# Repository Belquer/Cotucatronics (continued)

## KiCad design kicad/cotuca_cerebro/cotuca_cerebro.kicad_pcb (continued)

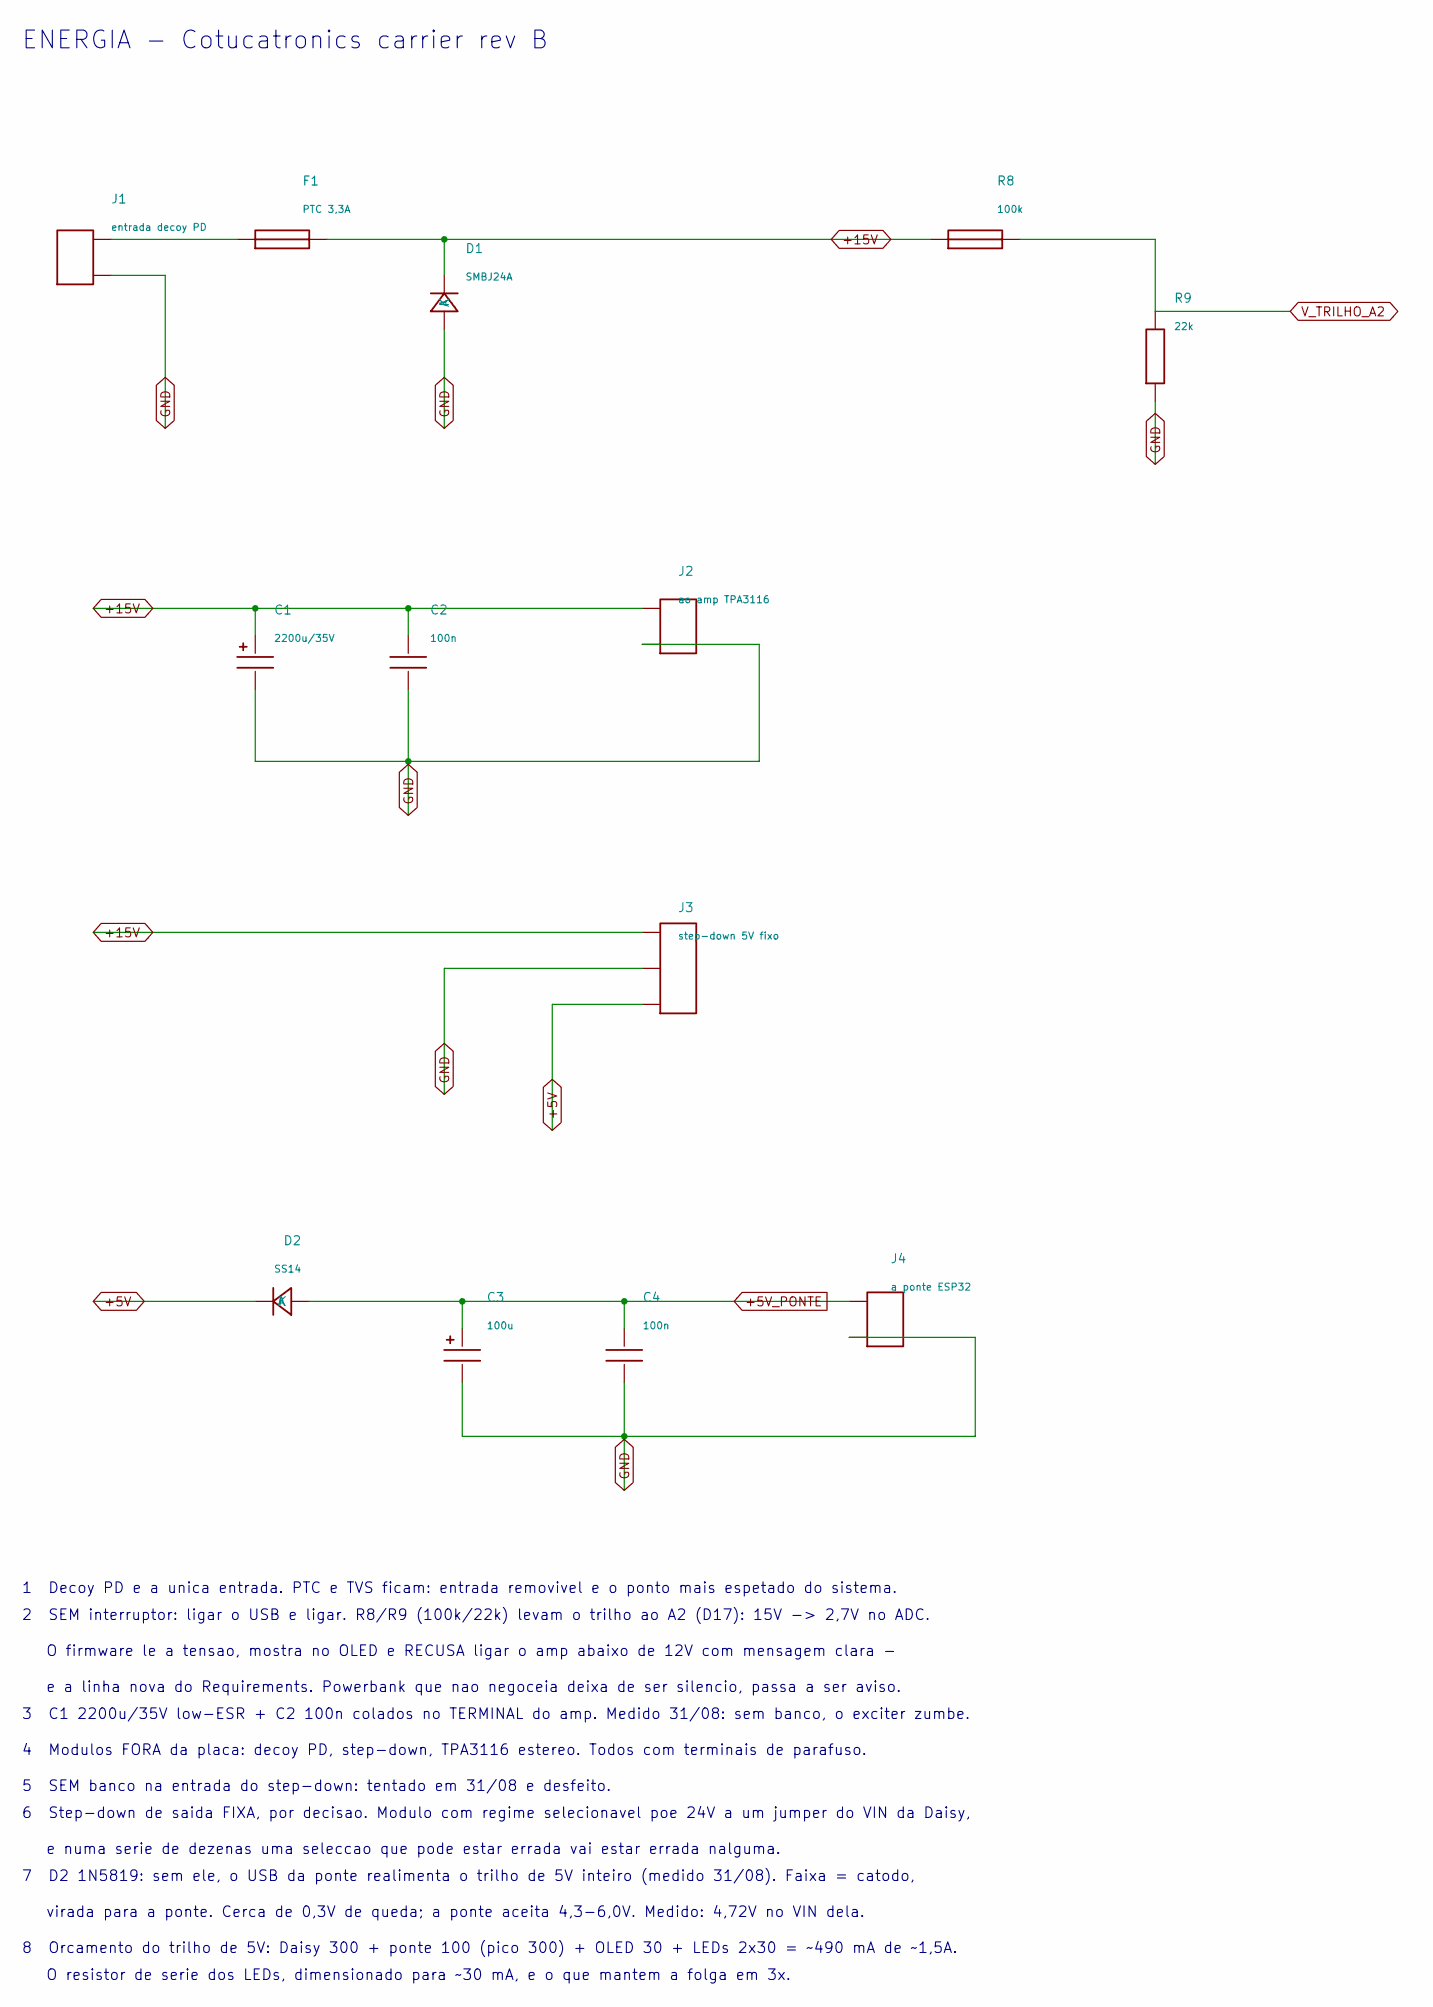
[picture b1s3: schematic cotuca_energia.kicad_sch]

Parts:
C1: 2200u/35V; CP_Radial_D16.0mm_P7.50mm; MPN EEU-FR1V222
C2, C4: 100n; C_0805_2012Metric
C3: 100u; CP_Radial_D6.3mm_P2.50mm; MPN EEU-FR1C101
D1: SMBJ24A; D_SMB; MPN SMBJ24A
D2: SS14; D_SMA; MPN SS14
F1: PTC 3,3A; Fuse_2920_7451Metric; MPN MF-LSMF300/24X-2
J1: entrada decoy PD; TerminalBlock_Phoenix_MKDS-1,5-2-5.08_1x02_P5.08mm_Horizont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; MPN 1715721
J2: ao amp TPA3116; TerminalBlock_Phoenix_MKDS-1,5-2-5.08_1x02_P5.08mm_Horizont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; MPN 1715721
J3: step-down 5V fixo; PinHeader_1x03_P2.54mm_Vertical; MPN 61304011121
J4: a ponte ESP32; PinHeader_1x02_P2.54mm_Vertical; MPN 61304011121
R8: 100k; R_0805_2012Metric
R9: 22k; R_0805_2012Metric

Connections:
+5V: D2.2 (A), J3.3; also elsewhere on the board
+5V_PONTE: C3.1, C4.1, D2.1 (K), J4.1; also elsewhere on the board
+15V: C1.1, C2.1, D1.1 (K), F1.2, J2.1, J3.1, R8.1; also elsewhere on the board
GND: C1.2, C2.2, C3.2, C4.2, D1.2 (A), J1.2, J2.2, J3.2, J4.2, R9.2; also elsewhere on the board
unnamed: F1.1, J1.1
V_TRILHO_A2: R8.2, R9.1; also elsewhere on the board

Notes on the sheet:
3 C1 2200u/35V low-ESR + C2 100n colados no TERMINAL do amp. Medido 31/08: sem banco, o exciter zumbe.
virada para a ponte. Cerca de 0,3V de queda; a ponte aceita 4,3-6,0V. Medido: 4,72V no VIN dela.
6 Step-down de saida FIXA, por decisao. Modulo com regime selecionavel poe 24V a um jumper do VIN da Daisy,
e numa serie de dezenas uma seleccao que pode estar errada vai estar errada nalguma.
O firmware le a tensao, mostra no OLED e RECUSA ligar o amp abaixo de 12V com mensagem clara -
5 SEM banco na entrada do step-down: tentado em 31/08 e desfeito.
8 Orcamento do trilho de 5V: Daisy 300 + ponte 100 (pico 300) + OLED 30 + LEDs 2x30 = ~490 mA de ~1,5A.
e a linha nova do Requirements. Powerbank que nao negoceia deixa de ser silencio, passa a ser aviso.
1 Decoy PD e a unica entrada. PTC e TVS ficam: entrada removivel e o ponto mais espetado do sistema.
2 SEM interruptor: ligar o USB e ligar. R8/R9 (100k/22k) levam o trilho ao A2 (D17): 15V -> 2,7V no ADC.
7 D2 1N5819: sem ele, o USB da ponte realimenta o trilho de 5V inteiro (medido 31/08). Faixa = catodo,
4 Modulos FORA da placa: decoy PD, step-down, TPA3116 estereo. Todos com terminais de parafuso.
ENERGIA - Cotucatronics carrier rev B
O resistor de serie dos LEDs, dimensionado para ~30 mA, e o que mantem a folga em 3x.

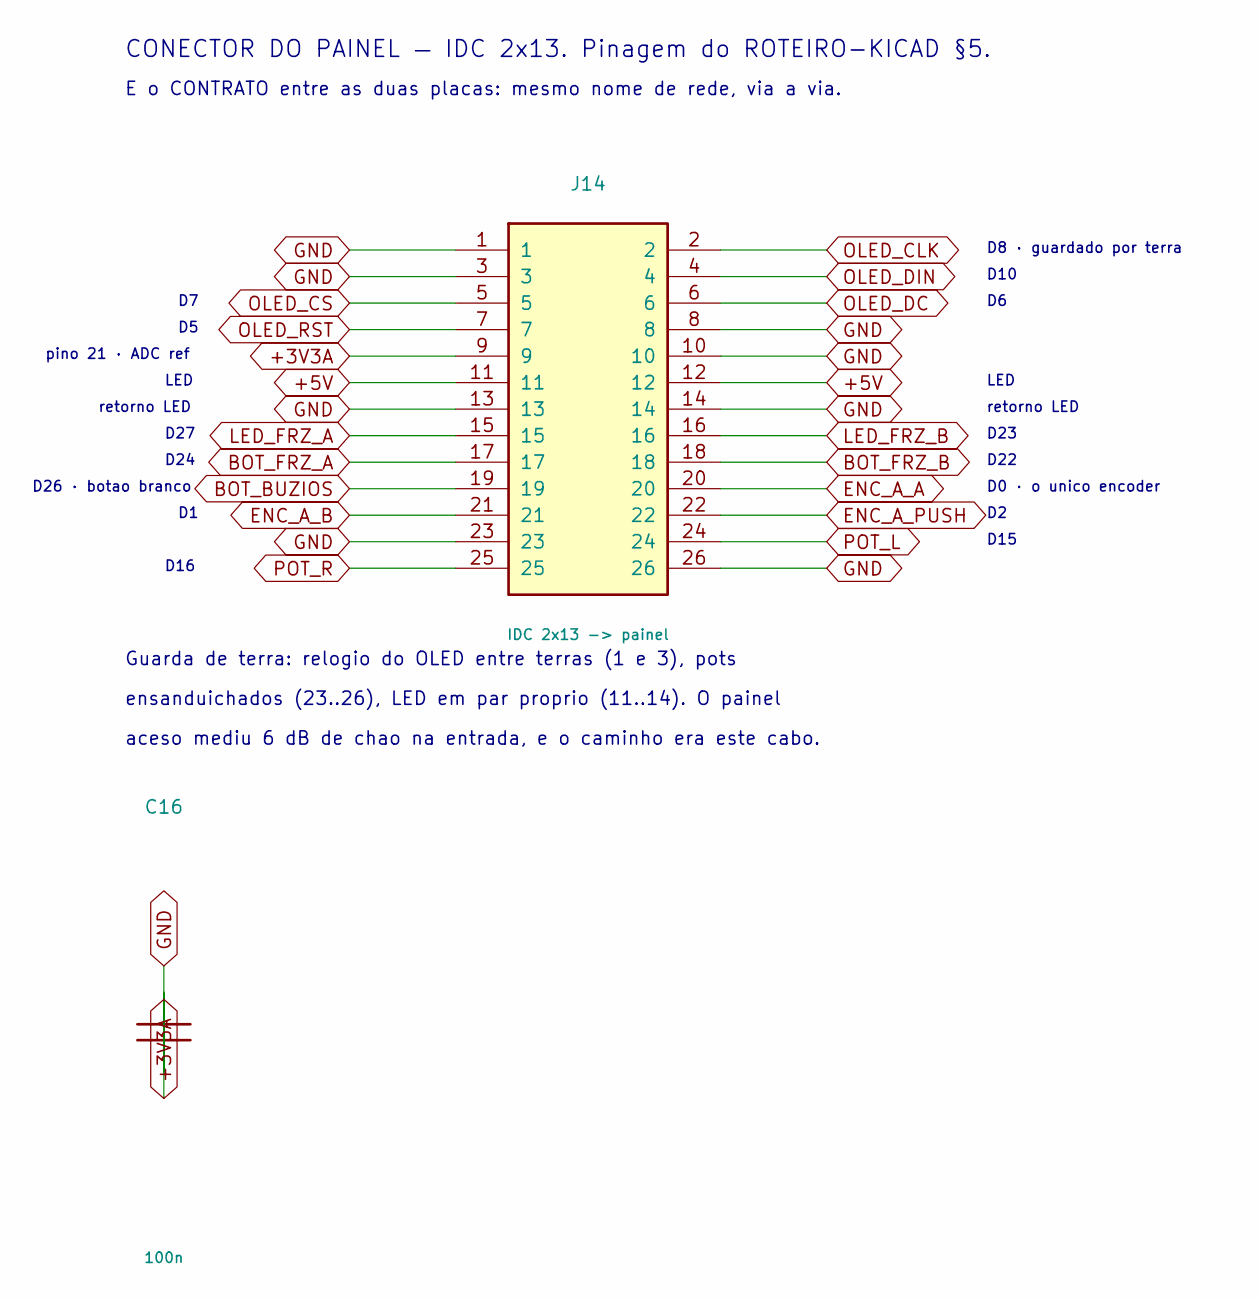
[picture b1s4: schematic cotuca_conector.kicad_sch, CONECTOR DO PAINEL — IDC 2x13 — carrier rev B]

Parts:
C16: 100n; C_0805_2012Metric
J14: IDC 2x13 -> painel; IDC-Header_2x13_P2.54mm_Vertical; MPN 61202621621

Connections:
+3V3A: C16.1, J14.9; also elsewhere on the board
+5V: J14.11, J14.12; also elsewhere on the board
BOT_BUZIOS: J14.19; also elsewhere on the board
BOT_FRZ_A: J14.17; also elsewhere on the board
BOT_FRZ_B: J14.18; also elsewhere on the board
ENC_A_A: J14.20; also elsewhere on the board
ENC_A_B: J14.21; also elsewhere on the board
ENC_A_PUSH: J14.22; also elsewhere on the board
GND: C16.2, J14.1, J14.3, J14.8, J14.10, J14.13, J14.14, J14.23, J14.26; also elsewhere on the board
LED_FRZ_A: J14.15; also elsewhere on the board
LED_FRZ_B: J14.16; also elsewhere on the board
OLED_CLK: J14.2; also elsewhere on the board
OLED_CS: J14.5; also elsewhere on the board
OLED_DC: J14.6; also elsewhere on the board
OLED_DIN: J14.4; also elsewhere on the board
OLED_RST: J14.7; also elsewhere on the board
POT_L: J14.24; also elsewhere on the board
POT_R: J14.25; also elsewhere on the board

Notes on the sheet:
D8 · guardado por terra
D10
pino 21 · ADC ref
LED
retorno LED
D27
D23
D24
D22
D26 · botao branco
D0 · o unico encoder
D15
D16
CONECTOR DO PAINEL — IDC 2x13. Pinagem do ROTEIRO-KICAD §5.
E o CONTRATO entre as duas placas: mesmo nome de rede, via a via.
Guarda de terra: relogio do OLED entre terras (1 e 3), pots
ensanduichados (23..26), LED em par proprio (11..14). O painel
aceso mediu 6 dB de chao na entrada, e o caminho era este cabo.

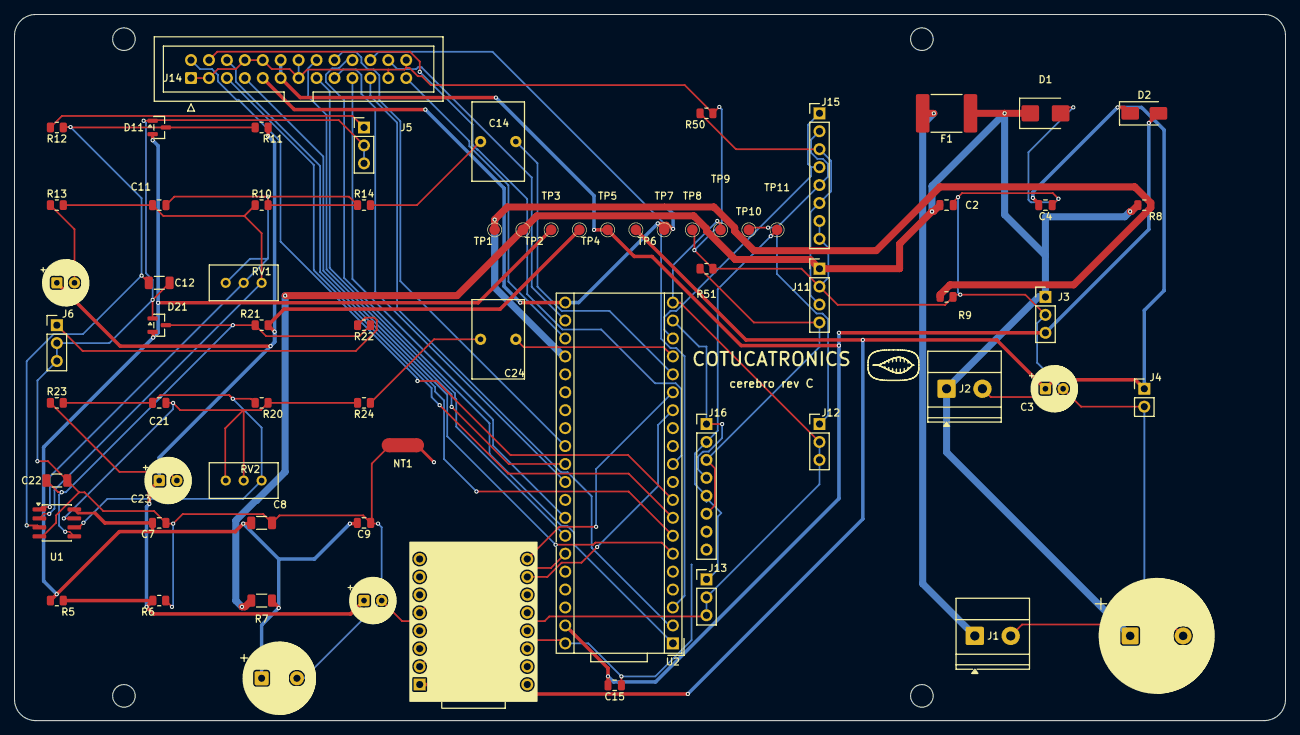
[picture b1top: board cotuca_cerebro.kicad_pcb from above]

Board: 2 copper layers, 180.0 x 100.0 mm, 74 parts (1 on the bottom side), 48 nets.

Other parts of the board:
H1, H2, H3, H4: MountingHole_3.2mm_M3

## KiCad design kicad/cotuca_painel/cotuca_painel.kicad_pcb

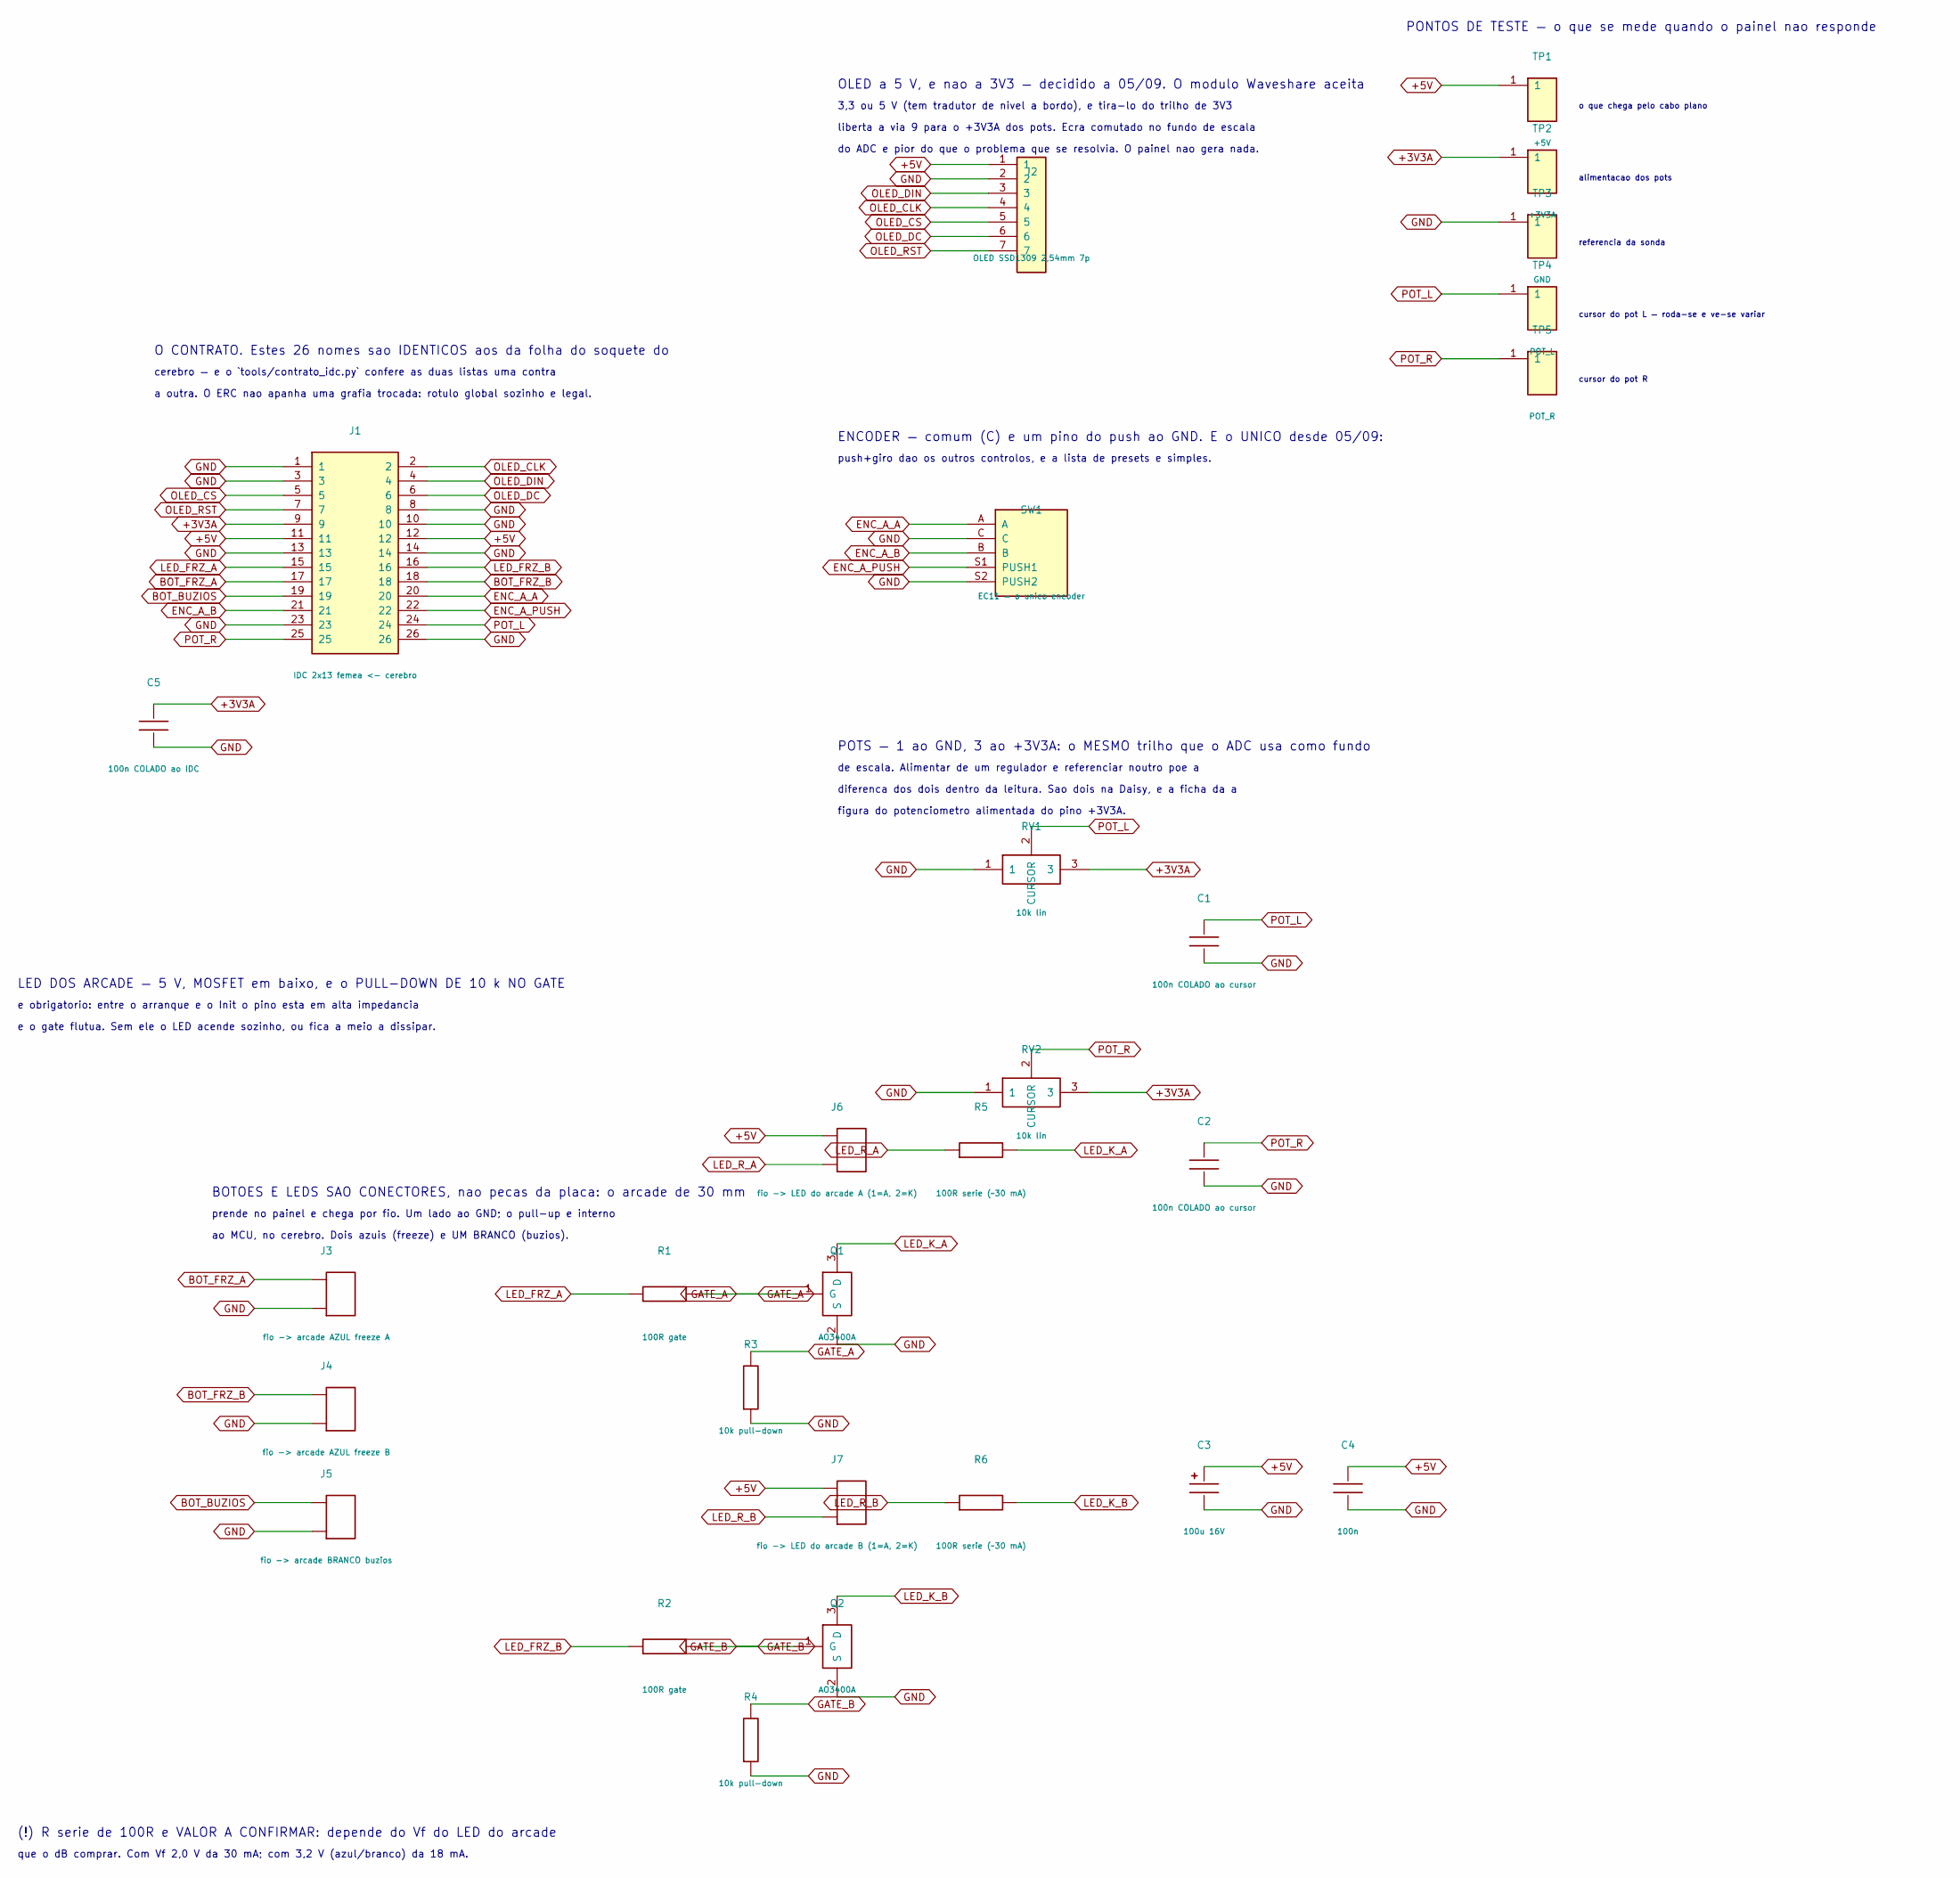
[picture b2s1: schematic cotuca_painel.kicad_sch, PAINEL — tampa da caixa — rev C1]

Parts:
C1, C2: 100n COLADO ao cursor; C_0805_2012Metric
C3: 100u 16V; CP_Radial_D6.3mm_P2.50mm; MPN EEU-FR1C101
C4: 100n; C_0805_2012Metric
C5: 100n COLADO ao IDC; C_0805_2012Metric
J1: IDC 2x13 femea <- cerebro; IDC-Header_2x13_P2.54mm_Vertical; MPN 61202621621
J2: OLED SSD1309 2,54mm 7p; PinHeader_1x07_P2.54mm_Vertical; MPN 53047-0710
J3: fio -> arcade AZUL freeze A; JST_XH_B2B-XH-A_1x02_P2.50mm_Vertical; MPN B2B-XH-A
J4: fio -> arcade AZUL freeze B; JST_XH_B2B-XH-A_1x02_P2.50mm_Vertical; MPN B2B-XH-A
J5: fio -> arcade BRANCO buzios; JST_XH_B2B-XH-A_1x02_P2.50mm_Vertical; MPN B2B-XH-A
J6: fio -> LED do arcade A (1=A, 2=K); JST_XH_B2B-XH-A_1x02_P2.50mm_Vertical; MPN B2B-XH-A
J7: fio -> LED do arcade B (1=A, 2=K); JST_XH_B2B-XH-A_1x02_P2.50mm_Vertical; MPN B2B-XH-A
Q1, Q2: AO3400A; SOT-23; MPN SI2302CDS-T1-GE3
R1, R2: 100R gate; R_0805_2012Metric
R3, R4: 10k pull-down; R_0805_2012Metric
R5, R6: 100R serie (~30 mA); R_1210_3225Metric
RV1, RV2: 10k lin; Potentiometer_Bourns_PTV09A-1_Single_Vertical; MPN PTV09A-1020S-B103
SW1: EC11 — o unico encoder; RotaryEncoder_Alps_EC11E-Switch_Vertical_H20mm; MPN EC11E15244G1
TP1: +5V; TestPoint_Pad_D1.5mm
TP2: +3V3A; TestPoint_Pad_D1.5mm
TP3: GND; TestPoint_Pad_D1.5mm
TP4: POT_L; TestPoint_Pad_D1.5mm
TP5: POT_R; TestPoint_Pad_D1.5mm

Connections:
+3V3A: C5.1, J1.9, RV1.3, RV2.3, TP2.1
+5V: C3.1, C4.1, J1.11, J1.12, J2.1, J6.1, J7.1, TP1.1
BOT_BUZIOS: J1.19, J5.1
BOT_FRZ_A: J1.17, J3.1
BOT_FRZ_B: J1.18, J4.1
ENC_A_A: J1.20, SW1.A
ENC_A_B: J1.21, SW1.B
ENC_A_PUSH: J1.22, SW1.S1 (PUSH1)
GATE_A: Q1.1 (G), R1.2, R3.1
GATE_B: Q2.1 (G), R2.2, R4.1
GND: C1.2, C2.2, C3.2, C4.2, C5.2, J1.1, J1.3, J1.8, J1.10, J1.13, J1.14, J1.23, J1.26, J2.2, J3.2, J4.2, J5.2, Q1.2 (S), Q2.2 (S), R3.2, R4.2, RV1.1, RV2.1, SW1.C, SW1.S2 (PUSH2), TP3.1
LED_FRZ_A: J1.15, R1.1
LED_FRZ_B: J1.16, R2.1
LED_K_A: Q1.3 (D), R5.2
LED_K_B: Q2.3 (D), R6.2
LED_R_A: J6.2, R5.1
LED_R_B: J7.2, R6.1
OLED_CLK: J1.2, J2.4
OLED_CS: J1.5, J2.5
OLED_DC: J1.6, J2.6
OLED_DIN: J1.4, J2.3
OLED_RST: J1.7, J2.7
POT_L: C1.1, J1.24, RV1.2 (CURSOR), TP4.1
POT_R: C2.1, J1.25, RV2.2 (CURSOR), TP5.1

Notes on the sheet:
O CONTRATO. Estes 26 nomes sao IDENTICOS aos da folha do soquete do
cerebro — e o `tools/contrato_idc.py` confere as duas listas uma contra
a outra. O ERC nao apanha uma grafia trocada: rotulo global sozinho e legal.
OLED a 5 V, e nao a 3V3 — decidido a 05/09. O modulo Waveshare aceita
3,3 ou 5 V (tem tradutor de nivel a bordo), e tira-lo do trilho de 3V3
liberta a via 9 para o +3V3A dos pots. Ecra comutado no fundo de escala
do ADC e pior do que o problema que se resolvia. O painel nao gera nada.
ENCODER — comum (C) e um pino do push ao GND. E o UNICO desde 05/09:
push+giro dao os outros controlos, e a lista de presets e simples.
POTS — 1 ao GND, 3 ao +3V3A: o MESMO trilho que o ADC usa como fundo
de escala. Alimentar de um regulador e referenciar noutro poe a
diferenca dos dois dentro da leitura. Sao dois na Daisy, e a ficha da a
figura do potenciometro alimentada do pino +3V3A.
BOTOES E LEDS SAO CONECTORES, nao pecas da placa: o arcade de 30 mm
prende no painel e chega por fio. Um lado ao GND; o pull-up e interno
ao MCU, no cerebro. Dois azuis (freeze) e UM BRANCO (buzios).
LED DOS ARCADE — 5 V, MOSFET em baixo, e o PULL-DOWN DE 10 k NO GATE
e obrigatorio: entre o arranque e o Init o pino esta em alta impedancia
e o gate flutua. Sem ele o LED acende sozinho, ou fica a meio a dissipar.
(!) R serie de 100R e VALOR A CONFIRMAR: depende do Vf do LED do arcade
que o dB comprar. Com Vf 2,0 V da 30 mA; com 3,2 V (azul/branco) da 18 mA.
o que chega pelo cabo plano
alimentacao dos pots
referencia da sonda
cursor do pot L — roda-se e ve-se variar
cursor do pot R
PONTOS DE TESTE — o que se mede quando o painel nao responde

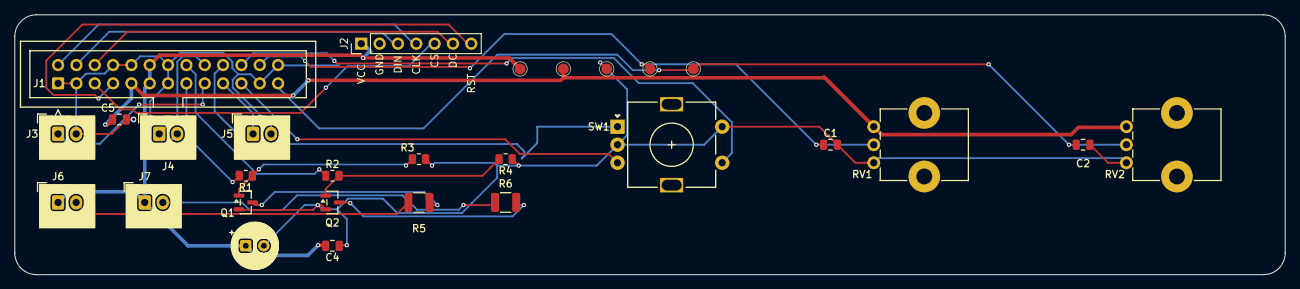
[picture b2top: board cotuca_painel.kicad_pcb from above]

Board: 2 copper layers, 176.0 x 36.0 mm, 28 parts (0 on the bottom side), 24 nets.

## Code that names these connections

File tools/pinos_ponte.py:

#!/usr/bin/env python3
"""pinos_ponte v0.1.0 — o firmware da ponte e a PLACA falam dos mesmos pinos?

    (Python do KiCad)  tools/pinos_ponte.py [--sabota]

POR QUE EXISTE, e custou uma tarde de bancada (2026-09-21).

O dB montou tudo, o iPad viu o `Cotucatronics` e ligou, mexeu nos parametros
do Loopy — e nada. A placa dizia a verdade no `board`:

    midi: 0 volta(s) com sobra · pico 0 de 128 bytes do anel
    midi tx: DESCARTES 70 | falhas 631   <-- a ponte esta ligada?

**Nunca chegou um byte.** O motivo: o `esp32/ponte/ponte.ino` v0.5.0 punha a
UART em `GPIO4/5/6` — escolha legitima de quando a ponte vivia em CINCO FIOS
SOLTOS — e a placa rev C liga o soquete `U3` em `IO20/IO21/IO3`. Dois
documentos, os dois corretos no seu tempo, e nenhuma ferramenta a compara-los.

⚠️ E o sintoma nao acusa a causa: **o BLE funciona na mesma**. O radio nao usa
estes pinos, entao o iPad liga, o Loopy mostra os controlos, e tudo parece bem
ate se perguntar a Daisy quantos bytes chegaram.

> Duas fontes do mesmo facto — o mapa de pinos — e a que nao corre e a que
> envelhece. Aqui as duas "correm": uma e gravada no ESP32, a outra e fabricada
> em cobre. Por isso a comparacao tem de ser um TERCEIRO, e e este ficheiro.

SO LE. Nao grava firmware nem placa.
"""
import os
import re
import sys

VERSAO = "0.1.0"
AQUI = os.path.dirname(os.path.abspath(__file__))
RAIZ = os.path.dirname(AQUI)
INO = os.path.join(RAIZ, "esp32", "ponte", "ponte.ino")
PCB = os.path.join(RAIZ, "kicad", "cotuca_cerebro", "cotuca_cerebro.kicad_pcb")

# o que cada constante do firmware TEM de casar, do lado da placa:
#   constante -> (pad do U3 esperado pela rede, rede)
# ⚠️ o sentido importa e e cruzado: o TX desta placa entra na rede que vai ao
# RX da Daisy. Trocar os dois nao queima nada — da silencio, que e o modo de
# falha mais caro de diagnosticar.
LIGACOES = {
    "PINO_TX":     "MIDI_RX",        # ESP transmite -> rede que chega ao RX da Daisy
    "PINO_RX":     "MIDI_TX",        # ESP recebe    <- rede que sai do TX da Daisy
    "PINO_STATUS": "PONTE_STATUS",
}


def do_firmware(texto=None):
    t = texto if texto is not None else open(INO, encoding="utf-8").read()
    achados = {}
    for nome in LIGACOES:
        m = re.search(r"static\s+const\s+int\s+%s\s*=\s*(\d+)\s*;" % nome, t)
        if not m:
            sys.exit("RECUSO: nao encontrei `%s` em %s — a leitura falhou, e "
                     "leitura incompleta nao aprova nada" % (nome, INO))
        achados[nome] = int(m.group(1))
    return achados


def da_placa():
    try:
        import pcbnew
    except ImportError:
        sys.exit("RECUSO: sem `pcbnew`. Corre com o Python do KiCad:\n"
                 "  /Applications/KiCad/KiCad.app/Contents/Frameworks/"
                 "Python.framework/Versions/3.9/bin/python3.9")
    b = pcbnew.LoadBoard(PCB)
    f = b.FindFootprintByReference("U3")
    if f is None:
        sys.exit("RECUSO: a placa nao tem `U3` — o soquete da ponte")
    por_rede = {}
    for p in f.Pads():
        rede = p.GetNetname()
        if rede:
            por_rede.setdefault(rede, []).append(p.GetNumber())
    return por_rede


def corre(sabota=False):
    fw = do_firmware()
    if sabota:
        fw["PINO_TX"] = 4           # o valor da v0.5.0, que a placa nao tem
    placa = da_placa()
    linhas, maus = [], 0
    for const, rede in sorted(LIGACOES.items()):
        pads = placa.get(rede, [])
        # os pads do SuperMini chamam-se IO20, IO21, IO3... — o numero e o que conta
        nums = []
        for pad in pads:
            m = re.search(r"(\d+)", pad)
            if m:
                nums.append(int(m.group(1)))
        ok = fw[const] in nums
        maus += not ok
        linhas.append("  %s %-12s firmware GPIO%-3d · placa %s (%s)"
                      % ("✓" if ok else "✗", const, fw[const],
                         "/".join("IO%d" % n for n in nums) or "—", rede))
    return linhas, maus


def main():
    print("pinos_ponte v%s — o firmware da ponte e a placa falam dos mesmos pinos?"
          % VERSAO)
    sabota = "--sabota" in sys.argv
    linhas, maus = corre()
    print("\n".join(linhas))
    if sabota:
        _l, m2 = corre(sabota=True)
        print("  sabotagem (PINO_TX de volta ao 4 da v0.5.0): %d -> %d divergencia(s)  %s"
              % (maus, m2, "✓ sabe dizer nao" if m2 > maus else "✗ NAO REPROVOU"))
        return 0 if m2 > maus else 1
    if maus:
        print("  ✗ %d divergencia(s): a ponte gravada NAO fala com esta placa.\n"
              "    Sintoma na bancada: o iPad liga e nada acontece; a Daisy diz\n"
              "    `pico 0 de 128 bytes do anel`. Regravar a ponte." % maus)
        return 1
    print("  ✓ o firmware da ponte casa com o cobre da placa")
    return 0


if __name__ == "__main__":
    raise SystemExit(main())
